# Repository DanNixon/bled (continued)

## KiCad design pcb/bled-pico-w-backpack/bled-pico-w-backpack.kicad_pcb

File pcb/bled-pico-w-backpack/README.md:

# Pico W backpack

"Backpack" style addon/carrier board for a Pi Pico W, with SD card slow and four WS2812 outputs.

## Parts

- [Raspberry Pi Pico 2/Pico 2 W](https://www.raspberrypi.com/documentation/microcontrollers/pico-series.html)
- https://jlcpcb.com/partdetail/XINGLIGHT-XL_1615RGBC2812B/C5349954
- https://jlcpcb.com/partdetail/SOFNG-TF15x15/C111196
- https://jlcpcb.com/partdetail/jianfu-TVAU10_025BR/C19271014
- https://jlcpcb.com/partdetail/MDD_Microdiode_Semiconductor-SS34/C8678
- https://jlcpcb.com/partdetail/16204-CL05A106MQ5NUNC/C15525
- https://jlcpcb.com/partdetail/50070-CL03A104KP3NNNC/C49062
- https://jlcpcb.com/partdetail/288614-RC01W473JT/C304547

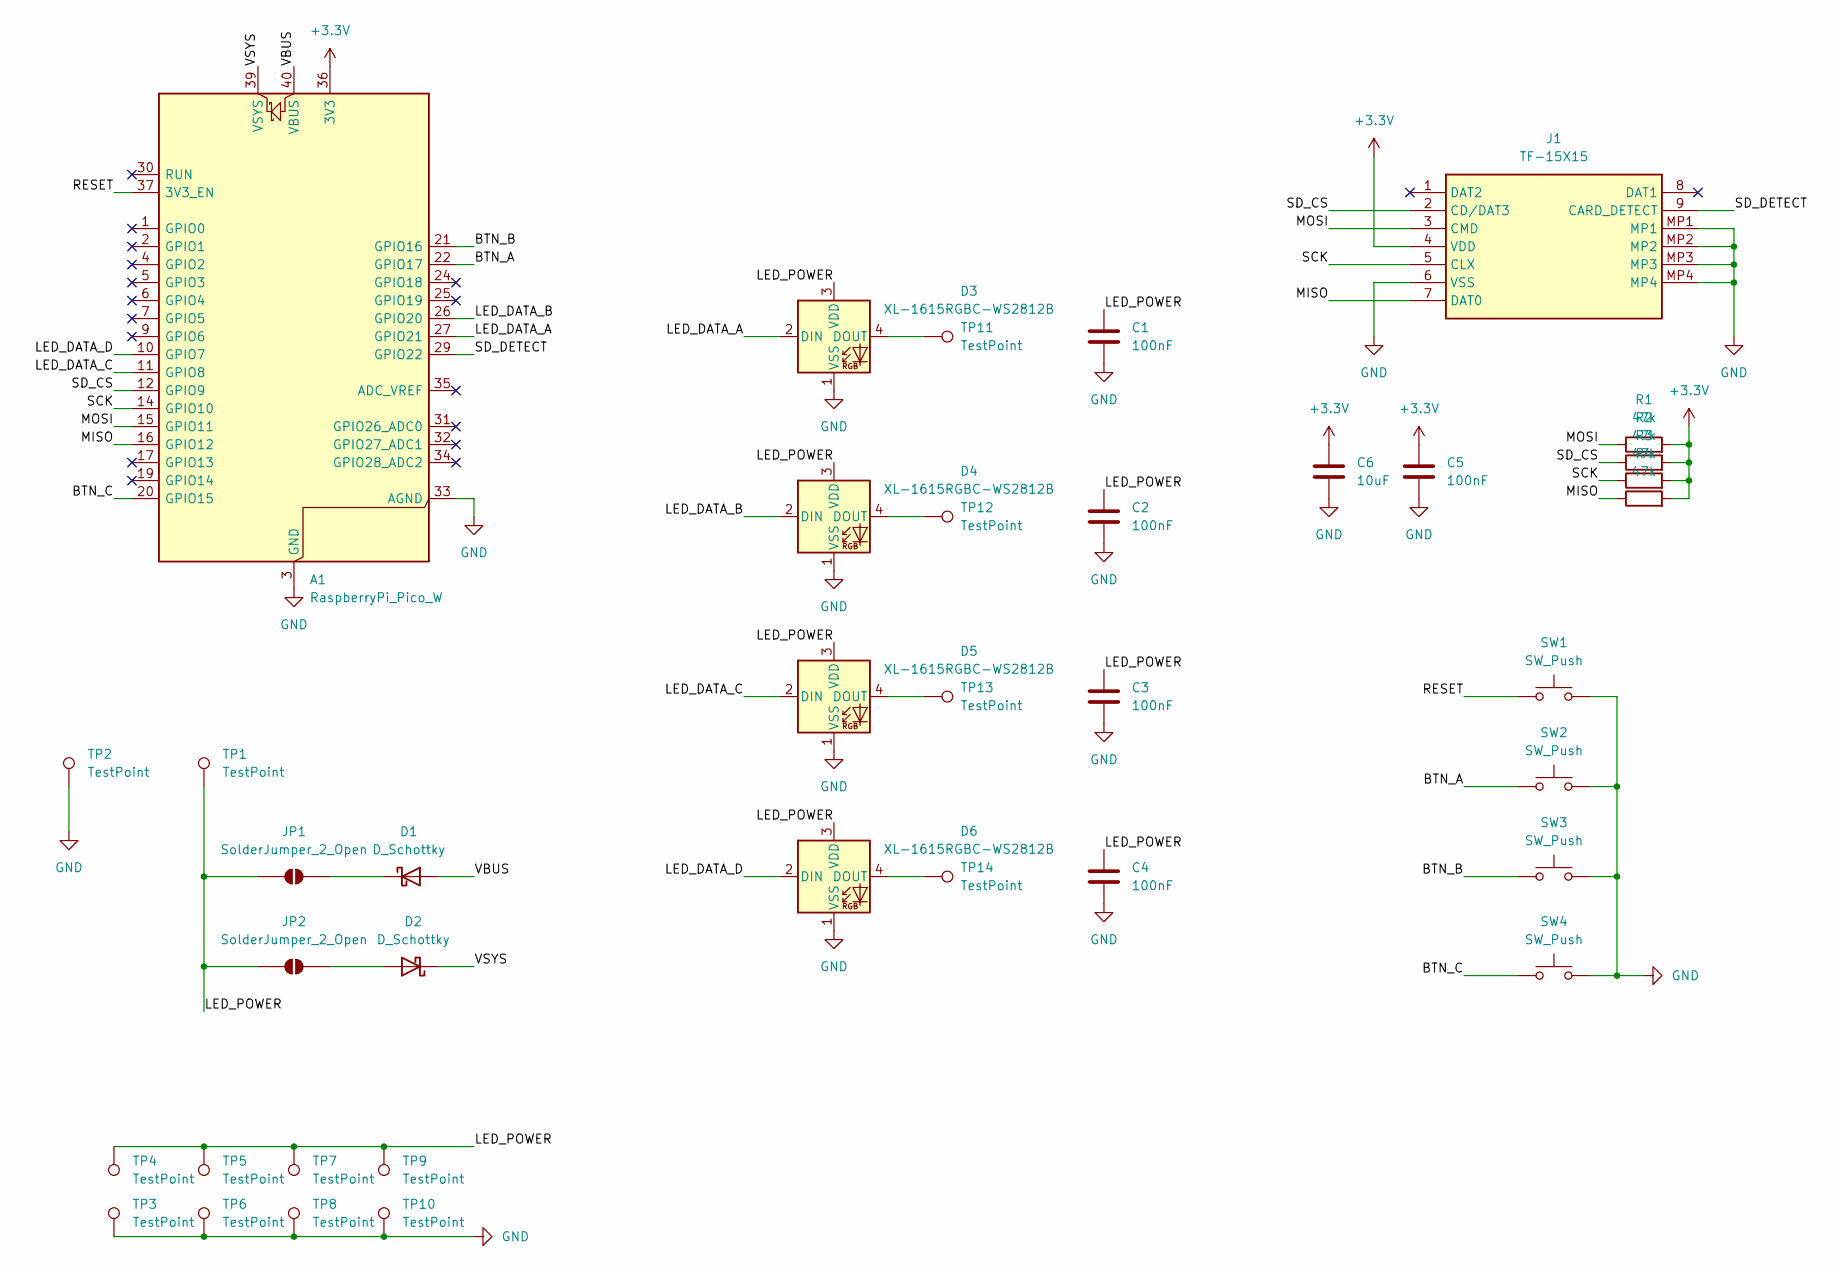
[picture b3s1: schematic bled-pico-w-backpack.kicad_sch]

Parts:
A1: RaspberryPi_Pico_W; RaspberryPi_Pico_Common_SMD
C1, C2, C3, C4, C5: 100nF; C_0201_0603Metric; LCSC C49062
C6: 10uF; C_0402_1005Metric; LCSC C15525
D1, D2: D_Schottky; D_SMA; LCSC C8678
D3, D4, D5, D6: XL-1615RGBC-WS2812B; XL-1615RGBC-2812B; LCSC C5349954
J1: TF-15X15; TF15X15; Manufacturer_Part_Number TF-15X15; LCSC C111196
JP1, JP2: SolderJumper_2_Open; SolderJumper-2_P1.3mm_Open_RoundedPad1.0x1.5mm
R1, R2, R3, R4: 47k; R_0201_0603Metric; LCSC C304547
SW1, SW2, SW3, SW4: SW_Push; TVAU10-025B-R; LCSC C19271014
TP1, TP2, TP3, TP4, TP5, TP6, TP7, TP8, TP9, TP10: TestPoint; TestPoint_Pad_2.5x2.5mm
TP11, TP12, TP13, TP14: TestPoint; TestPoint_Pad_D2.0mm

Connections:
+3.3V: A1.36 (3V3), C5.1, C6.1, J1.4 (VDD), R1.2, R2.2, R3.2, R4.2
/BTN_A: A1.22 (GPIO17), SW2.1
/BTN_B: A1.21 (GPIO16), SW3.1
/BTN_C: A1.20 (GPIO15), SW4.1
/LED_DATA_A: A1.27 (GPIO21), D3.2 (DIN)
/LED_DATA_B: A1.26 (GPIO20), D4.2 (DIN)
/LED_DATA_C: A1.11 (GPIO8), D5.2 (DIN)
/LED_DATA_D: A1.10 (GPIO7), D6.2 (DIN)
/LED_POWER: C1.1, C2.1, C3.1, C4.1, D3.3 (VDD), D4.3 (VDD), D5.3 (VDD), D6.3 (VDD), JP1.2 (B), JP2.1 (A), TP1.1 (1_1), TP4.1 (1_1), TP5.1 (1_1), TP7.1 (1_1), TP9.1 (1_1)
/MISO: A1.16 (GPIO12), J1.7 (DAT0), R4.1
/MOSI: A1.15 (GPIO11), J1.3 (CMD), R1.1
/RESET: A1.37 (3V3_EN), SW1.1
/SCK: A1.14 (GPIO10), J1.5 (CLX), R3.1
/SD_CS: A1.12 (GPIO9), J1.2 (CD/DAT3), R2.1
/SD_DETECT: A1.29 (GPIO22), J1.9 (CARD_DETECT)
/VBUS: A1.40 (VBUS), D1.2 (A)
/VSYS: A1.39 (VSYS), D2.1 (K)
GND: A1.3 (GND), A1.8 (GND), A1.13 (GND), A1.18 (GND), A1.23 (GND), A1.28 (GND), A1.33 (AGND), A1.38 (GND), C1.2, C2.2, C3.2, C4.2, C5.2, C6.2, D3.1 (VSS), D4.1 (VSS), D5.1 (VSS), D6.1 (VSS), J1.6 (VSS), J1.MP1, J1.MP2, J1.MP3, J1.MP4, SW1.2, SW2.2, SW3.2, SW4.2, TP2.1 (1_1), TP3.1 (1_1), TP6.1 (1_1), TP8.1 (1_1), TP10.1 (1_1)
unnamed: D1.1 (K), JP1.1 (A)
unnamed: D2.2 (A), JP2.2 (B)
unnamed: D3.4 (DOUT), TP11.1 (1_1)
unnamed: D4.4 (DOUT), TP12.1 (1_1)
unnamed: D5.4 (DOUT), TP13.1 (1_1)
unnamed: D6.4 (DOUT), TP14.1 (1_1)

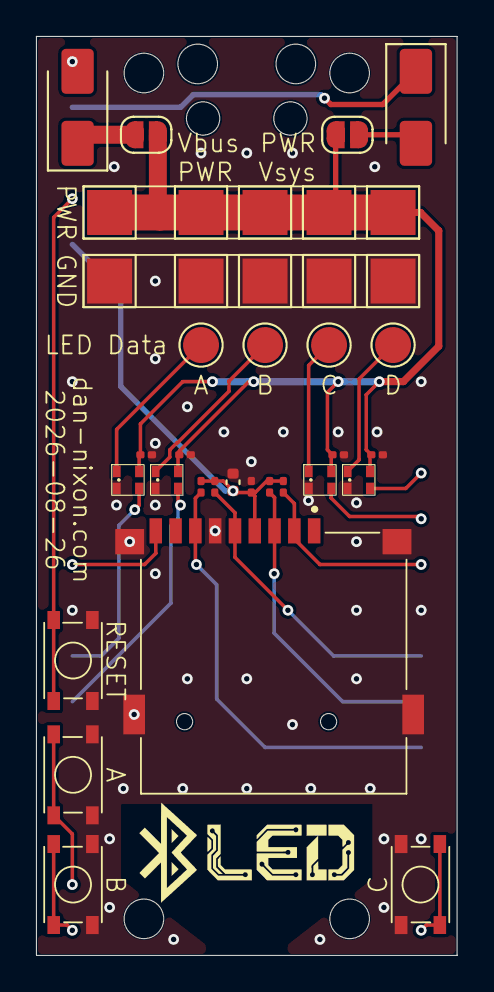
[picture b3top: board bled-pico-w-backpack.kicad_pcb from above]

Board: 2 copper layers, 23.4 x 51.1 mm, 38 parts (1 on the bottom side), 24 nets.

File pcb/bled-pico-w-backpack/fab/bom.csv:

Comment,Designator,Footprint,LCSC
TestPoint,"TP1,TP2,TP3,TP4,TP5,TP6,TP7,TP8,TP9,TP10",TestPoint:TestPoint_Pad_2.5x2.5mm,
100nF,"C1,C2,C3,C4,C5",Capacitor_SMD:C_0201_0603Metric,C49062
TestPoint,"TP11,TP12,TP13,TP14",TestPoint:TestPoint_Pad_D2.0mm,
SW_Push,"SW1,SW2,SW3,SW4",bled:TVAU10-025B-R,C19271014
D_Schottky,"D1,D2",Diode_SMD:D_SMA,C8678
47k,"R1,R2,R3,R4",Resistor_SMD:R_0201_0603Metric,C304547
XL-1615RGBC-WS2812B,"D3,D4,D5,D6",bled:XL-1615RGBC-2812B,C5349954
10uF,C6,Capacitor_SMD:C_0402_1005Metric,C15525
RaspberryPi_Pico_W,A1,Module:RaspberryPi_Pico_Common_SMD,
TF-15X15,J1,TF15X15,C111196
